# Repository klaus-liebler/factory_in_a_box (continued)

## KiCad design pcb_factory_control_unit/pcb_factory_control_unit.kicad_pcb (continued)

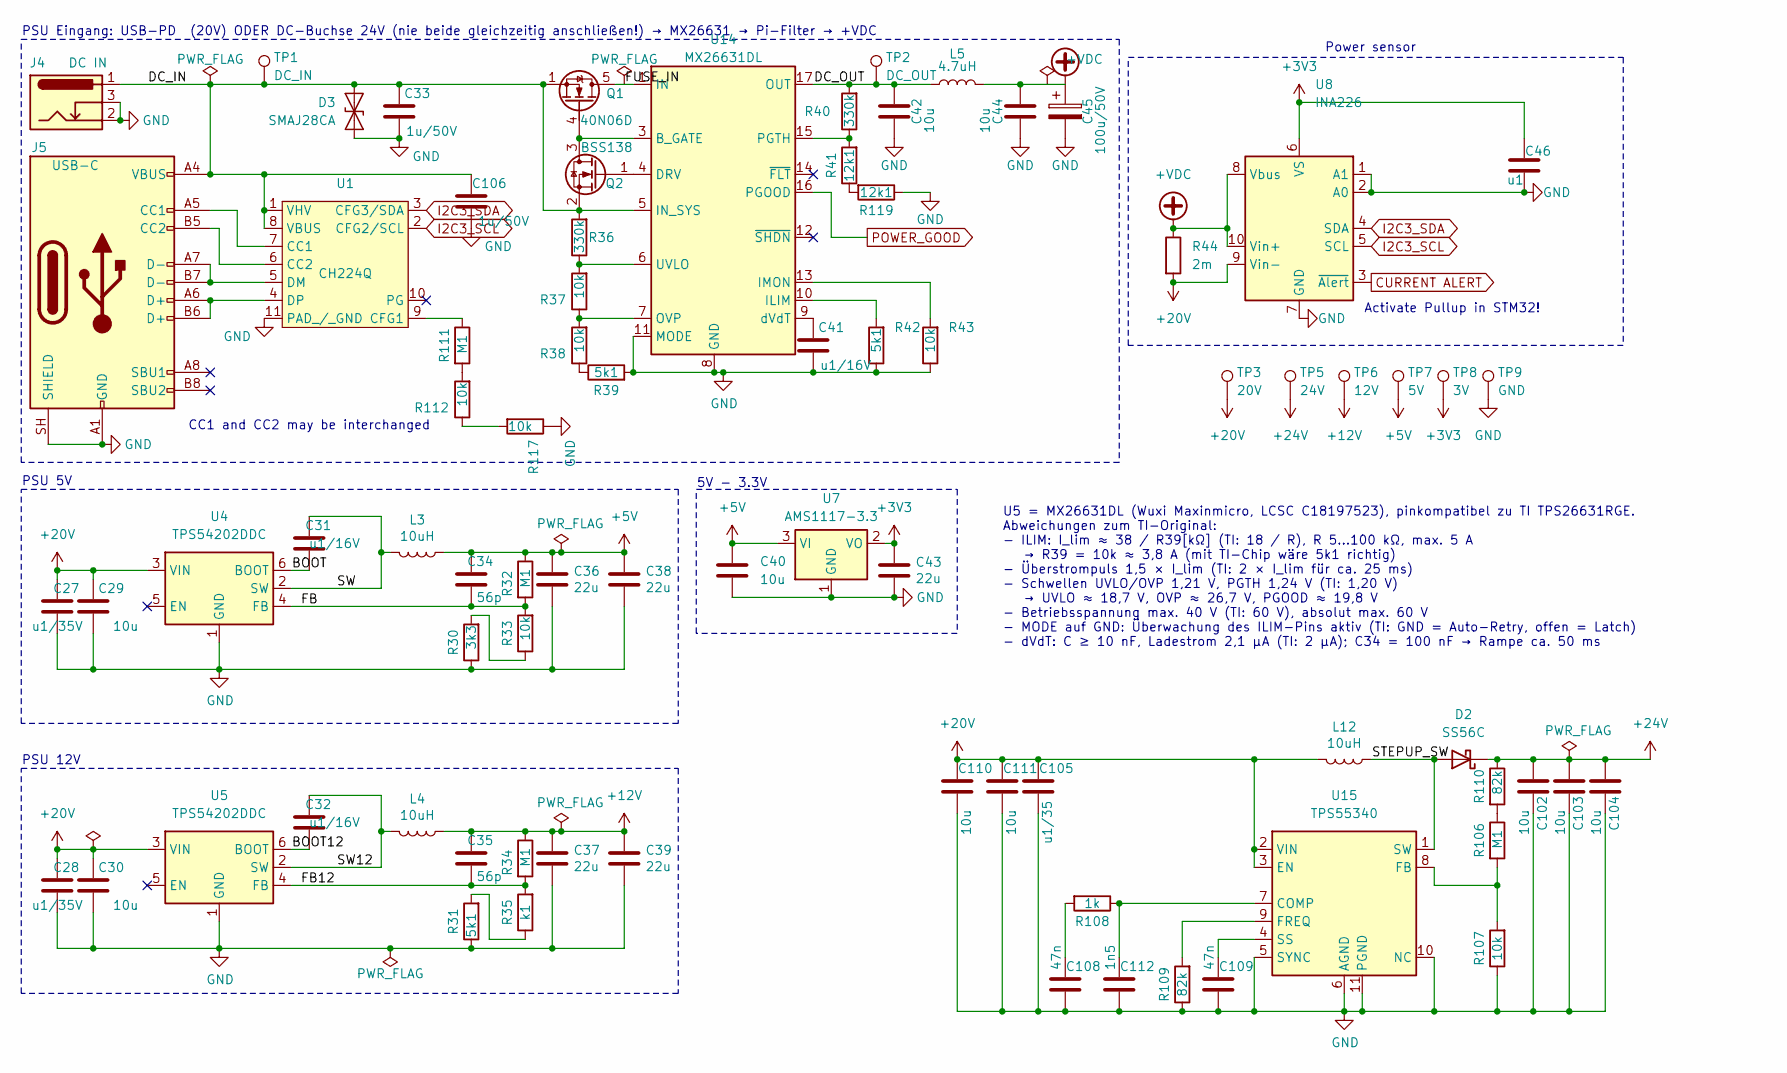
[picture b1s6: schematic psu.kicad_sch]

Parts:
C27, C28: u1/35V; C_0805_2012Metric; MPN CC0805KRX7R9BB104; LCSC C49678
C29, C30, C40, C110, C111: 10u; C_0805_2012Metric; MPN CGA0805X5R106K500MT; LCSC C6119889
C31, C32, C41: u1/16V; C_0402_1005Metric; MPN CL05B104KO5NNNC; LCSC C1525
C33, C106: 1u/50V; C_0805_2012Metric; MPN CL21B105KBFNNNE; LCSC C28323
C34, C35: 56p; C_0402_1005Metric; MPN CC0402JRNPO9BN560; LCSC C107007
C36, C37, C38, C39, C43: 22u; C_0805_2012Metric; MPN CL21A226MAQNNNE; LCSC C45783
C42, C44, C102, C103, C104: 10u; C_1210_3225Metric; MPN GRM32ER71H106KA12L; LCSC C77102
C45: 100u/50V; CP_Elec_8x10; MPN EEE-FK1H101P; LCSC C178548
C46: u1; C_0402_1005Metric; MPN CL05B104KO5NNNC; LCSC C1525
C105: u1/35; C_0805_2012Metric; MPN CC0805KRX7R9BB104; LCSC C49678
C108, C109: 47n; C_0402_1005Metric; MPN CL05B473KO5NNNC; LCSC C307434
C112: 1n5; C_0402_1005Metric; MPN CL05B152KB5NNNC; LCSC C23967
D2: SS56C; D_SMC; LCSC C24138
D3: SMAJ28CA; D_SMA; MPN SMAJ28CA; LCSC C19077546
J4: DC IN; BarrelJack_Horizontal; MPN DC-005 2.0
J5: USB-C; USB_C_Receptacle_HRO_TYPE-C-31-M-12_smaller; MPN TYPE-C-31-M-12; LCSC C165948
L3, L4, L12: 10uH; L_Abracon_ASPI-0630LR; MPN FXL0650-100-M; LCSC C475521
L5: 4.7uH; L_Bourns_SRP1245A; LCSC C54620181
Q1: 40N06D; VSON-8_3.3x3.3mm_P0.65mm_NexFET; MPN 40N06D; LCSC C7543836
Q2: BSS138; SOT-23; MPN BSS138LT1G; LCSC C82045
R30: 3k3; R_0402_1005Metric; MPN 0402WGF3301TCE; LCSC C25890
R31, R39, R42: 5k1; R_0402_1005Metric; MPN 0402WGF5101TCE; LCSC C25905
R32, R34, R106, R111: M1; R_0402_1005Metric; MPN 0402WGF1003TCE; LCSC C25741
R33, R37, R38, R43, R107, R112, R117: 10k; R_0402_1005Metric; MPN 0402WGF1002TCE; LCSC C25744
R35: k1; R_0402_1005Metric; MPN 0402WGF1000TCE; LCSC C25076
R36, R40: 330k; R_0402_1005Metric; MPN 0402WGF3303TCE; LCSC C25778
R41, R119: 12k1; R_0402_1005Metric; LCSC C25852
R44: 2m; R_1206_3216Metric; LCSC C844294
R108: 1k; R_0402_1005Metric; MPN 0402WGF1001TCE; LCSC C11702
R109, R110: 82k; R_0402_1005Metric; MPN 0402WGF8202TCE; LCSC C4142
TP1: DC_IN; TestPoint_Loop_D1.80mm_Drill1.0mm_Beaded
TP2: DC_OUT; TestPoint_Loop_D1.80mm_Drill1.0mm_Beaded
TP3: 20V; TestPoint_Loop_D1.80mm_Drill1.0mm_Beaded
TP5: 24V; TestPoint_Loop_D1.80mm_Drill1.0mm_Beaded
TP6: 12V; TestPoint_Loop_D1.80mm_Drill1.0mm_Beaded
TP7: 5V; TestPoint_Loop_D1.80mm_Drill1.0mm_Beaded
TP8: 3V; TestPoint_Loop_D1.80mm_Drill1.0mm_Beaded
TP9: GND; TestPoint_Loop_D1.80mm_Drill1.0mm_Beaded
U1: CH224Q; Texas_DSQ0010A_WSON-10-1EP_2x2mm_P0.4mm_EP0.9x1.5mm_Thermal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; LCSC C46061833
U4, U5: TPS54202DDC; SOT-23-6; MPN TPS54202DDCR; LCSC C191884
U7: AMS1117-3.3; SOT-223-3_TabPin2; LCSC C6186
U8: INA226; TSSOP-10_3x3mm_P0.5mm; LCSC C49851
U14: MX26631DL; Texas_RGE0024H_VQFN-24-1EP_4x4mm_P0.5mm_EP2.7x2.7mm_Thermal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; MPN MX26631DL; LCSC C18197523
U15: TPS55340; WQFN-16-1EP_3x3mm_P0.5mm_EP1.68x1.68mm_ThermalVias; MPN TPS55340RTER; LCSC C169167

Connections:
+3V3: C43.1, C46.1, TP8.1 (1_1), U7.2 (VO), U8.6 (VS); also elsewhere on the board
+5V: C34.2, C36.1, C38.1, C40.1, L3.1, R32.1, TP7.1 (1_1), U7.3 (VI); also elsewhere on the board
+12V: C35.2, C37.1, C39.1, L4.1, R34.1, TP6.1 (1_1); also elsewhere on the board
+20V: C27.2, C28.2, C29.2, C30.2, C105.2, C110.2, C111.2, L12.2, R44.2, TP3.1 (1_1), U4.3 (VIN), U5.3 (VIN), U8.9 (Vin-), U15.2 (VIN), U15.3 (EN); also elsewhere on the board
+24V: C102.1, C103.1, C104.1, D2.1 (K), R110.1, TP5.1 (1_1); also elsewhere on the board
+VDC: C44.1, C45.1, L5.2, R44.1, U8.8 (Vbus), U8.10 (Vin+)
/psu/BOOT: C31.1, U4.6 (BOOT)
/psu/BOOT12: C32.1, U5.6 (BOOT)
/psu/DC_IN: C33.2, C106.2, D3.2 (A2), J4.1, J5.A4 (VBUS), J5.A9 (VBUS), J5.B4 (VBUS), J5.B9 (VBUS), Q1.1 (S), Q1.2 (S), Q1.3 (S), Q2.2 (S), R36.2, TP1.1 (1_1), U1.1 (VHV), U1.8 (VBUS), U14.5 (IN_SYS)
/psu/DC_OUT: C42.1, L5.1, R40.2, TP2.1 (1_1), U14.17 (OUT), U14.18 (OUT)
/psu/FB: C34.1, R32.2, R33.2, U4.4 (FB)
/psu/FB12: C35.1, R34.2, R35.2, U5.4 (FB)
/psu/FUSE_IN: Q1.5 (D), U14.1 (IN), U14.2 (IN)
/psu/STEPUP_SW: D2.2 (A), L12.1, U15.1 (SW), U15.15 (SW), U15.16 (SW)
/psu/SW: C31.2, L3.2, U4.2 (SW)
/psu/SW12: C32.2, L4.2, U5.2 (SW)
CURRENT ALERT: U8.3 (~Alert); also elsewhere on the board
GND: C27.1, C28.1, C29.1, C30.1, C33.1, C36.2, C37.2, C38.2, C39.2, C40.2, C41.1, C42.2, C43.2, C44.2, C45.2, C46.2, C102.2, C103.2, C104.2, C105.1, C106.1, C108.1, C109.1, C110.1, C111.1, C112.1, D3.1 (A1), J4.2, J4.3, J5.A1 (GND), J5.A12 (GND), J5.B1 (GND), J5.B12 (GND), J5.SH (SHIELD), R30.1, R31.1, R39.2, R42.1, R43.1, R107.1, R109.1, R117.1, R119.1, TP9.1 (1_1), U1.11 (PAD_/_GND), U4.1 (GND), U5.1 (GND), U7.1 (GND), U8.1 (A1), U8.2 (A0), U8.7 (GND), U14.8 (GND), U14.11 (MODE), U14.25 (GND), U15.5 (SYNC), U15.6 (AGND), U15.10 (NC), U15.11 (PGND), U15.12 (PGND), U15.13 (PGND), U15.14 (NC), U15.17 (AGND); also elsewhere on the board
I2C3_SCL: U1.2 (CFG2/SCL), U8.5 (SCL); also elsewhere on the board
I2C3_SDA: U1.3 (CFG3/SDA), U8.4 (SDA); also elsewhere on the board
unnamed: C108.2, R108.2
unnamed: J5.A5 (CC1), U1.7 (CC1)
unnamed: J5.B5 (CC2), U1.6 (CC2)
unnamed: Q1.4 (G), Q2.3 (D), U14.3 (B_GATE)
unnamed: Q2.1 (G), U14.4 (DRV)
unnamed: R30.2, R33.1
unnamed: R31.2, R35.1
unnamed: R38.1, R39.1
unnamed: R106.1, R110.2
unnamed: R111.2, R112.2
unnamed: R112.1, R117.2
unnamed: R41.1, R119.2
unnamed: R111.1, U1.9 (CFG1)
unnamed: J5.A7 (D-), J5.B7 (D-), U1.5 (DM)
unnamed: J5.A6 (D+), J5.B6 (D+), U1.4 (DP)
unnamed: R42.2, U14.10 (ILIM)
unnamed: R43.2, U14.13 (IMON)
unnamed: R37.1, R38.2, U14.7 (OVP)
unnamed: R40.1, R41.2, U14.15 (PGTH)
unnamed: R36.1, R37.2, U14.6 (UVLO)
unnamed: C41.2, U14.9 (dVdT)
unnamed: C112.2, R108.1, U15.7 (COMP)
unnamed: R106.2, R107.2, U15.8 (FB)
unnamed: R109.2, U15.9 (FREQ)
unnamed: C109.2, U15.4 (SS)
POWER_GOOD: U14.16 (PGOOD); also elsewhere on the board

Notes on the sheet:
PSU 5V
Power sensor
U5 = MX26631DL (Wuxi Maxinmicro, LCSC C18197523), pinkompatibel zu TI TPS26631RGE. Abweichungen zum TI-Original: - ILIM: I_lim ≈ 38 / R39[kΩ] (TI: 18 / R), R 5…100 kΩ, max. 5 A → R39 = 10k ≈ 3,8 A (mit TI-Chip wäre 5k1 richtig) - Überstrompuls 1,5 × I_lim (TI: 2 × I_lim für ca. 25 ms) - Schwellen U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
PSU Eingang: USB-PD (20V) ODER DC-Buchse 24V (nie beide gleichzeitig anschließen!) → MX26631 → Pi-Filter → +VDC
PSU 12V
Activate Pullup in STM32!
CC1 and CC2 may be interchanged
5V - 3.3V

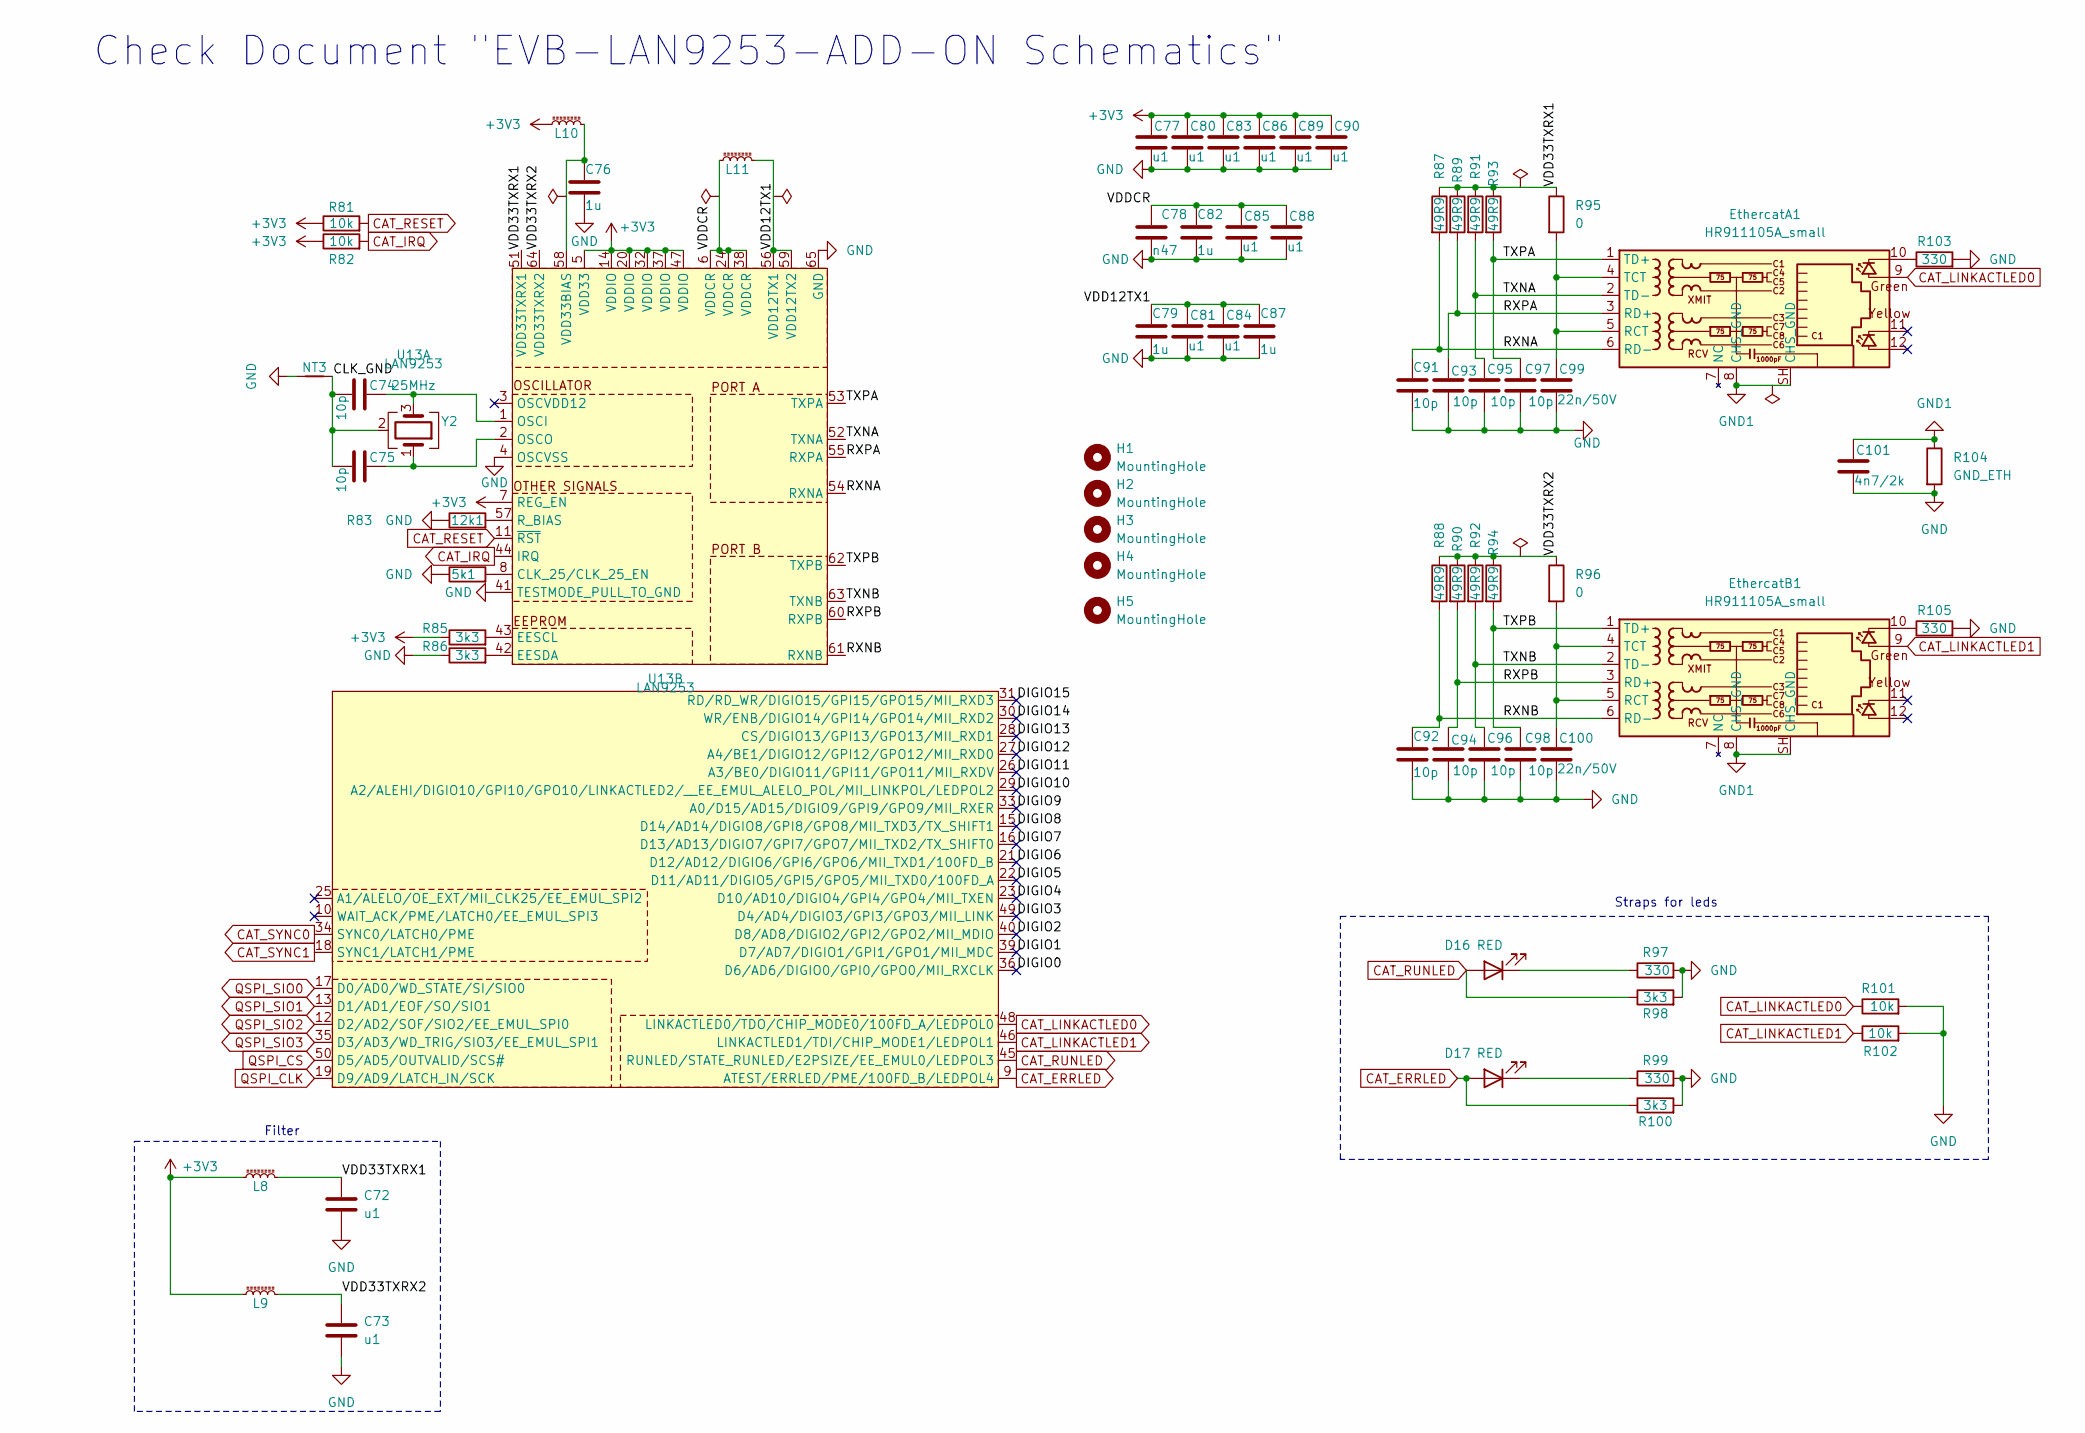
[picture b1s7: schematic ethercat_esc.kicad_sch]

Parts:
C72, C73, C77, C80, C81, C83, C84, C85, C86, C88, C89, C90: u1; C_0402_1005Metric; MPN CL05B104KO5NNNC; LCSC C1525
C74, C75, C91, C92, C93, C94, C95, C96, C97, C98: 10p; C_0402_1005Metric; MPN CC0402JRNPO9BN100; LCSC C106199
C76, C79, C82, C87: 1u; C_0402_1005Metric; MPN CL05A105KA5NQNC; LCSC C52923
C78: n47; C_0402_1005Metric; MPN GRM1555C1H471JA01D; LCSC C76971
C99, C100: 22n/50V; C_0402_1005Metric; MPN 0402B223K500NT; LCSC C1532
C101: 4n7/2k; C_0805_2012Metric_Pad1.18x1.45mm_HandSolder
D16, D17: RED; LED_1206_3216Metric_ReverseMount_Hole1.8x2.4mm; MPN P2-1206RTCS2-0.9T-F; LCSC C2827254
EthercatA1: HR911105A_small; RJ45_HANRUN_HR911105A; LCSC C12074
EthercatB1: HR911105A_small; RJ45_HANRUN_HR911105A; LCSC C12074
H1, H2, H3, H4: MountingHole; MountingHole_4.3mm_M4_DIN965
H5: MountingHole; barrel_jack_positive_polarity
L8, L9, L10, L11: 220R@100M; L_0603_1608Metric; MPN BLM18PG221SN1D; LCSC C80165
NT3: NetTie_2; NetTie-2_SMD_Pad0.5mm
R81, R82, R101, R102: 10k; R_0402_1005Metric; MPN 0402WGF1002TCE; LCSC C25744
R83: 12k1; R_0402_1005Metric; LCSC C25852
R84: 5k1; R_0402_1005Metric; MPN 0402WGF5101TCE; LCSC C25905
R85, R86, R98, R100: 3k3; R_0402_1005Metric; MPN 0402WGF3301TCE; LCSC C25890
R87, R88, R89, R90, R91, R92, R93, R94: 49R9; R_0402_1005Metric; LCSC C25120
R95, R96: 0; R_0805_2012Metric_Pad1.20x1.40mm_HandSolder; MPN 0805W8F0000T5E; LCSC C17477
R97, R99, R103, R105: 330; R_0402_1005Metric; MPN 0402WGF3300TCE; LCSC C25104
R104: GND_ETH; R_0805_2012Metric_Pad1.20x1.40mm_HandSolder
U13: LAN9253; QFN-64-1EP_9x9mm_P0.5mm_EP6x6mm_ThermalVias; MPN LAN9253-I/R4X; LCSC C5745149
Y2: 25MHz; Crystal_SMD_2016-4Pin_2.0x1.6mm; LCSC C19711739

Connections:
+3V3: C77.1, C80.1, C83.1, C86.1, C89.1, C90.1, L8.1, L9.1, L10.1, R81.1, R82.1, R85.1, U13.5 (VDD33), U13.7 (REG_EN), U13.14 (VDDIO), U13.20 (VDDIO), U13.32 (VDDIO), U13.37 (VDDIO), U13.47 (VDDIO); also elsewhere on the board
/EtherCAT/CLK_GND: C74.2, C75.2, NT3.2, Y2.2 (G), Y2.4 (G)
/EtherCAT/DIGIO0: U13.36 (D6/AD6/DIGIO0/GPI0/GPO0/MII_RXCLK)
/EtherCAT/DIGIO1: U13.39 (D7/AD7/DIGIO1/GPI1/GPO1/MII_MDC)
/EtherCAT/DIGIO2: U13.40 (D8/AD8/DIGIO2/GPI2/GPO2/MII_MDIO)
/EtherCAT/DIGIO3: U13.49 (D4/AD4/DIGIO3/GPI3/GPO3/MII_LINK)
/EtherCAT/DIGIO4: U13.23 (D10/AD10/DIGIO4/GPI4/GPO4/MII_TXEN)
/EtherCAT/DIGIO5: U13.22 (D11/AD11/DIGIO5/GPI5/GPO5/MII_TXD0/100F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)
/EtherCAT/DIGIO6: U13.21 (D12/AD12/DIGIO6/GPI6/GPO6/MII_TXD1/100F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)
/EtherCAT/DIGIO7: U13.16 (D13/AD13/DIGIO7/GPI7/GPO7/MII_TXD2/TX_S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)
/EtherCAT/DIGIO8: U13.15 (D14/AD14/DIGIO8/GPI8/GPO8/MII_TXD3/TX_S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)
/EtherCAT/DIGIO9: U13.33 (A0/D15/AD15/DIGIO9/GPI9/GPO9/MII_RXER)
/EtherCAT/DIGIO10: U13.29 (A2/ALEHI/DIGIO10/GPI10/GPO10/LINKACTLED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)
/EtherCAT/DIGIO11: U13.26 (A3/BE0/DIGIO11/GPI11/GPO11/MII_RXDV)
/EtherCAT/DIGIO12: U13.27 (A4/BE1/DIGIO12/GPI12/GPO12/MII_RXD0)
/EtherCAT/DIGIO13: U13.28 (CS/DIGIO13/GPI13/GPO13/MII_RXD1)
/EtherCAT/DIGIO14: U13.30 (WR/ENB/DIGIO14/GPI14/GPO14/MII_RXD2)
/EtherCAT/DIGIO15: U13.31 (RD/RD_WR/DIGIO15/GPI15/GPO15/MII_RXD3)
/EtherCAT/RXNA: C91.1, EthercatA1.6 (RD-), R87.2, U13.54 (RXNA)
/EtherCAT/RXNB: C92.1, EthercatB1.6 (RD-), R88.2, U13.61 (RXNB)
/EtherCAT/RXPA: C93.1, EthercatA1.3 (RD+), R89.2, U13.55 (RXPA)
/EtherCAT/RXPB: C94.1, EthercatB1.3 (RD+), R90.2, U13.60 (RXPB)
/EtherCAT/TXNA: C95.1, EthercatA1.2 (TD-), R91.2, U13.52 (TXNA)
/EtherCAT/TXNB: C96.1, EthercatB1.2 (TD-), R92.2, U13.63 (TXNB)
/EtherCAT/TXPA: C97.1, EthercatA1.1 (TD+), R93.2, U13.53 (TXPA)
/EtherCAT/TXPB: C98.1, EthercatB1.1 (TD+), R94.2, U13.62 (TXPB)
/EtherCAT/VDD12TX1: C79.1, C81.1, C84.1, C87.1, L11.2, U13.56 (VDD12TX1), U13.59 (VDD12TX2)
/EtherCAT/VDD33TXRX1: C72.1, L8.2, R87.1, R89.1, R91.1, R93.1, R95.1, U13.51 (VDD33TXRX1)
/EtherCAT/VDD33TXRX2: C73.1, L9.2, R88.1, R90.1, R92.1, R94.1, R96.1, U13.64 (VDD33TXRX2)
/EtherCAT/VDDCR: C78.1, C82.1, C85.1, C88.1, L11.1, U13.6 (VDDCR), U13.24 (VDDCR), U13.38 (VDDCR)
CAT_ERRLED: D17.2 (A), R100.1, U13.9 (ATEST/ERRLED/PME/100FD_B/LEDPOL4)
CAT_IRQ: R82.2, U13.44 (IRQ); also elsewhere on the board
CAT_LINKACTLED0: EthercatA1.9, R101.1, U13.48 (LINKACTLED0/TDO/CHIP_MODE0/100FD_A/LEDP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)
CAT_LINKACTLED1: EthercatB1.9, R102.1, U13.46 (LINKACTLED1/TDI/CHIP_MODE1/LEDPOL1)
CAT_RESET: R81.2, U13.11 (~RST); also elsewhere on the board
CAT_RUNLED: D16.2 (A), R98.1, U13.45 (RUNLED/STATE_RUNLED/E2PSIZE/EE_EMUL0/LE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)
CAT_SYNC0: U13.34 (SYNC0/LATCH0/PME); also elsewhere on the board
CAT_SYNC1: U13.18 (SYNC1/LATCH1/PME); also elsewhere on the board
GND: C72.2, C73.2, C76.2, C77.2, C78.2, C79.2, C80.2, C81.2, C82.2, C83.2, C84.2, C85.2, C86.2, C87.2, C88.2, C89.2, C90.2, C91.2, C92.2, C93.2, C94.2, C95.2, C96.2, C97.2, C98.2, C99.2, C100.2, C101.2, NT3.1, R83.1, R84.1, R86.1, R97.2, R98.2, R99.2, R100.2, R101.2, R102.2, R103.2, R104.2, R105.2, U13.4 (OSCVSS), U13.41 (TESTMODE_PULL_TO_GND), U13.65 (GND); also elsewhere on the board
GND1: C101.1, EthercatA1.8 (CHS_GND), EthercatA1.SH (CHS_GND), EthercatB1.8 (CHS_GND), EthercatB1.SH (CHS_GND), R104.1; also elsewhere on the board
unnamed: D16.1 (K), R97.1
unnamed: D17.1 (K), R99.1
unnamed: EthercatA1.10, R103.1
unnamed: C99.1, EthercatA1.4 (TCT), EthercatA1.5 (RCT), R95.2
unnamed: EthercatB1.10, R105.1
unnamed: C100.1, EthercatB1.4 (TCT), EthercatB1.5 (RCT), R96.2
unnamed: R84.2, U13.8 (CLK_25/CLK_25_EN)
unnamed: R85.2, U13.43 (EESCL)
unnamed: R86.2, U13.42 (EESDA)
unnamed: C74.1, U13.1 (OSCI), Y2.3
unnamed: C75.1, U13.2 (OSCO), Y2.1
unnamed: R83.2, U13.57 (R_BIAS)
unnamed: C76.1, L10.2, U13.58 (VDD33BIAS)
QSPI_CLK: U13.19 (D9/AD9/LATCH_IN/SCK); also elsewhere on the board
QSPI_CS: U13.50 (D5/AD5/OUTVALID/SCS#); also elsewhere on the board
QSPI_SIO0: U13.17 (D0/AD0/WD_STATE/SI/SIO0); also elsewhere on the board
QSPI_SIO1: U13.13 (D1/AD1/EOF/SO/SIO1); also elsewhere on the board
QSPI_SIO2: U13.12 (D2/AD2/SOF/SIO2/EE_EMUL_SPI0); also elsewhere on the board
QSPI_SIO3: U13.35 (D3/AD3/WD_TRIG/SIO3/EE_EMUL_SPI1); also elsewhere on the board

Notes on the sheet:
Straps for leds
Filter
Check Document "EVB-LAN9253-ADD-ON Schematics"

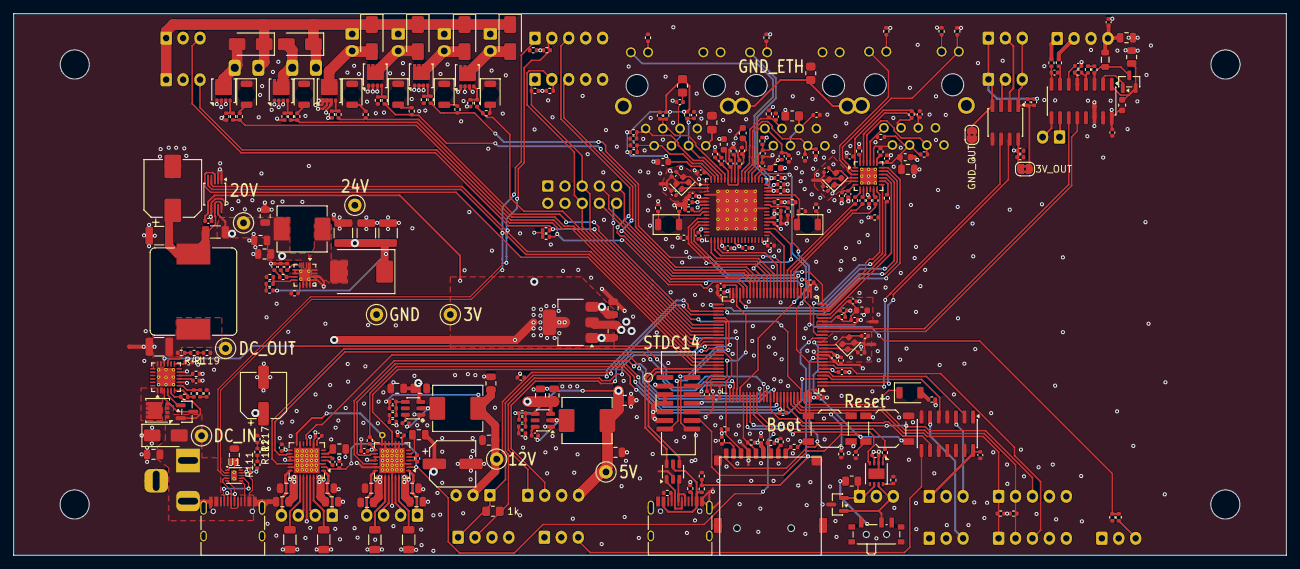
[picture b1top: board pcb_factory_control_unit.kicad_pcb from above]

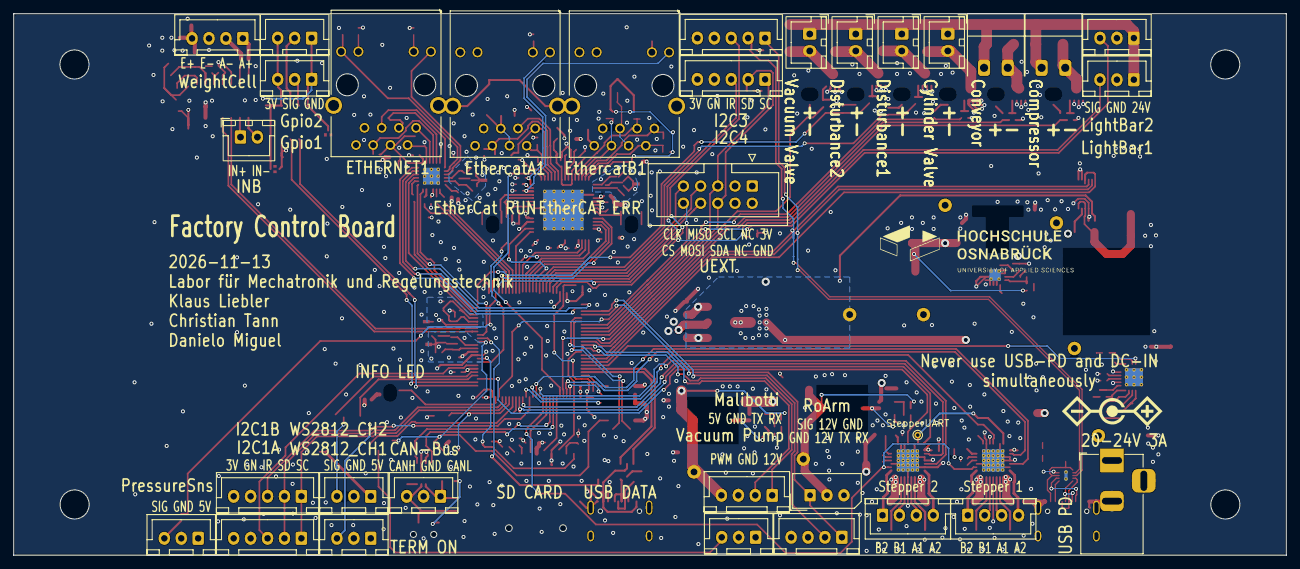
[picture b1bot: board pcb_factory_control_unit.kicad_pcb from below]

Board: 4 copper layers, 188.0 x 80.0 mm, 352 parts (33 on the bottom side), 252 nets.

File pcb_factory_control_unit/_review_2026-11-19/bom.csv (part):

"Reference","Value","Footprint","MPN","LCSC","QUANTITY","DNP","Manufacturer"
"C1","u1","Capacitor_SMD:C_0402_1005Metric","CL05B104KO5NNNC","C1525","1","","Samsung Electro-Mechanics"
"C2","u1","Capacitor_SMD:C_0402_1005Metric","CL05B104KO5NNNC","C1525","1","","Samsung Electro-Mechanics"
"C3","u1","Capacitor_SMD:C_0402_1005Metric","CL05B104KO5NNNC","C1525","1","","Samsung Electro-Mechanics"
"C4","1u","Capacitor_SMD:C_0402_1005Metric","CL05A105KA5NQNC","C52923","1","","Samsung Electro-Mechanics"
"C5","u1","Capacitor_SMD:C_0402_1005Metric","CL05B104KO5NNNC","C1525","1","","Samsung Electro-Mechanics"
"C6","u1","Capacitor_SMD:C_0402_1005Metric","CL05B104KO5NNNC","C1525","1","","Samsung Electro-Mechanics"
"C7","u1","Capacitor_SMD:C_0402_1005Metric","CL05B104KO5NNNC","C1525","1","","Samsung Electro-Mechanics"
"C8","u1","Capacitor_SMD:C_0402_1005Metric","CL05B104KO5NNNC","C1525","1","","Samsung Electro-Mechanics"
"C9","u1","Capacitor_SMD:C_0402_1005Metric","CL05B104KO5NNNC","C1525","1","","Samsung Electro-Mechanics"
"C11","4u7","Capacitor_SMD:C_0402_1005Metric","","C307423","1","",""
"C12","u1","Capacitor_SMD:C_0402_1005Metric","CL05B104KO5NNNC","C1525","1","","Samsung Electro-Mechanics"
"C13","2u2","Capacitor_SMD:C_0402_1005Metric","CL05A225MQ5NSNC","C12530","1","","Samsung Electro-Mechanics"
"C14","1u","Capacitor_SMD:C_0402_1005Metric","CL05A105KA5NQNC","C52923","1","","Samsung Electro-Mechanics"
"C15","2u2","Capacitor_SMD:C_0402_1005Metric","CL05A225MQ5NSNC","C12530","1","","Samsung Electro-Mechanics"
"C16","u1","Capacitor_SMD:C_0402_1005Metric","CL05B104KO5NNNC","C1525","1","","Samsung Electro-Mechanics"
"C17","u1","Capacitor_SMD:C_0402_1005Metric","CL05B104KO5NNNC","C1525","1","","Samsung Electro-Mechanics"
"C18","10p","Capacitor_SMD:C_0402_1005Metric","CC0402JRNPO9BN100","C106199","1","","YAGEO"
"C19","10n","Capacitor_SMD:C_0402_1005Metric","FCC0402B103K500AT","C5137480","1","","FOJAN"
"C20","10p","Capacitor_SMD:C_0402_1005Metric","CC0402JRNPO9BN100","C106199","1","","YAGEO"
"C21","1u","Capacitor_SMD:C_0402_1005Metric","CL05A105KA5NQNC","C52923","1","","Samsung Electro-Mechanics"
"C22","n47","Capacitor_SMD:C_0402_1005Metric","GRM1555C1H471JA01D","C76971","1","","Murata Electronics"
"C23","10n","Capacitor_SMD:C_0402_1005Metric","FCC0402B103K500AT","C5137480","1","","FOJAN"
"C24","10n","Capacitor_SMD:C_0402_1005Metric","FCC0402B103K500AT","C5137480","1","","FOJAN"
"C25","10u","Capacitor_SMD:C_0805_2012Metric","CGA0805X5R106K500MT","C6119889","1","","HRE"
"C26","22n/50V","Capacitor_SMD:C_0402_1005Metric","0402B223K500NT","C1532","1","","FH(Guangdong Fenghua Advanced Tech)"
"C27","u1/35V","Capacitor_SMD:C_0805_2012Metric","CC0805KRX7R9BB104","C49678","1","","YAGEO"
"C28","u1/35V","Capacitor_SMD:C_0805_2012Metric","CC0805KRX7R9BB104","C49678","1","","YAGEO"
"C29","10u","Capacitor_SMD:C_0805_2012Metric","CGA0805X5R106K500MT","C6119889","1","","HRE"
"C30","10u","Capacitor_SMD:C_0805_2012Metric","CGA0805X5R106K500MT","C6119889","1","","HRE"
"C31","u1/16V","Capacitor_SMD:C_0402_1005Metric","CL05B104KO5NNNC","C1525","1","","Samsung Electro-Mechanics"
"C32","u1/16V","Capacitor_SMD:C_0402_1005Metric","CL05B104KO5NNNC","C1525","1","","Samsung Electro-Mechanics"
"C33","1u/50V","Capacitor_SMD:C_0805_2012Metric","CL21B105KBFNNNE","C28323","1","","Samsung Electro-Mechanics"
"C34","56p","Capacitor_SMD:C_0402_1005Metric","CC0402JRNPO9BN560","C107007","1","","YAGEO"
"C35","56p","Capacitor_SMD:C_0402_1005Metric","CC0402JRNPO9BN560","C107007","1","","YAGEO"
"C36","22u","Capacitor_SMD:C_0805_2012Metric","CL21A226MAQNNNE","C45783","1","","Samsung Electro-Mechanics"
"C37","22u","Capacitor_SMD:C_0805_2012Metric","CL21A226MAQNNNE","C45783","1","","Samsung Electro-Mechanics"
"C38","22u","Capacitor_SMD:C_0805_2012Metric","CL21A226MAQNNNE","C45783","1","","Samsung Electro-Mechanics"
"C39","22u","Capacitor_SMD:C_0805_2012Metric","CL21A226MAQNNNE","C45783","1","","Samsung Electro-Mechanics"
"C40","10u","Capacitor_SMD:C_0805_2012Metric","CGA0805X5R106K500MT","C6119889","1","","HRE"
"C41","u1/16V","Capacitor_SMD:C_0402_1005Metric","CL05B104KO5NNNC","C1525","1","","Samsung Electro-Mechanics"
"C42","10u","Capacitor_SMD:C_1210_3225Metric","GRM32ER71H106KA12L","C77102","1","","Murata"
"C43","22u","Capacitor_SMD:C_0805_2012Metric","CL21A226MAQNNNE","C45783","1","","Samsung Electro-Mechanics"
"C44","10u","Capacitor_SMD:C_1210_3225Metric","GRM32ER71H106KA12L","C77102","1","","Murata"
"C45","100u/50V","Capacitor_SMD:CP_Elec_8x10","EEE-FK1H101P","C178548","1","","Panasonic"
"C46","u1","Capacitor_SMD:C_0402_1005Metric","CL05B104KO5NNNC","C1525","1","","Samsung Electro-Mechanics"
"C47","u1/50V","Capacitor_SMD:C_0805_2012Metric","CC0805KRX7R9BB104","C49678","1","","YAGEO"
"C48","u1/50V","Capacitor_SMD:C_0805_2012Metric","CC0805KRX7R9BB104","C49678","1","","YAGEO"
"C49","u1","Capacitor_SMD:C_0402_1005Metric","CL05B104KO5NNNC","C1525","1","","Samsung Electro-Mechanics"
"C50","u1","Capacitor_SMD:C_0402_1005Metric","CL05B104KO5NNNC","C1525","1","","Samsung Electro-Mechanics"
"C51","u1/35V","Capacitor_SMD:C_0805_2012Metric","CC0805KRX7R9BB104","C49678","1","","YAGEO"
"C52","u1/35V","Capacitor_SMD:C_0805_2012Metric","CC0805KRX7R9BB104","C49678","1","","YAGEO"
"C53","u1/35V","Capacitor_SMD:C_0805_2012Metric","CC0805KRX7R9BB104","C49678","1","","YAGEO"
"C54","u1/35V","Capacitor_SMD:C_0805_2012Metric","CC0805KRX7R9BB104","C49678","1","","YAGEO"
"C55","2u2","Capacitor_SMD:C_0402_1005Metric","CL05A225MQ5NSNC","C12530","1","","Samsung Electro-Mechanics"
"C56","22n/50V","Capacitor_SMD:C_0402_1005Metric","0402B223K500NT","C1532","1","","FH(Guangdong Fenghua Advanced Tech)"
"C57","2u2","Capacitor_SMD:C_0402_1005Metric","CL05A225MQ5NSNC","C12530","1","","Samsung Electro-Mechanics"
"C58","22n/50V","Capacitor_SMD:C_0402_1005Metric","0402B223K500NT","C1532","1","","FH(Guangdong Fenghua Advanced Tech)"
"C59","22u/35V","Capacitor_SMD:C_0805_2012Metric","CGA0805X5R226M350MT","C6119901","1","","HRE"
"C60","22u/35V","Capacitor_SMD:C_0805_2012Metric","CGA0805X5R226M350MT","C6119901","1","","HRE"
"C61","22u/35V","Capacitor_SMD:C_0805_2012Metric","CGA0805X5R226M350MT","C6119901","1","","HRE"
"C62","22u/35V","Capacitor_SMD:C_0805_2012Metric","CGA0805X5R226M350MT","C6119901","1","","HRE"
"C63","u1","Capacitor_SMD:C_0402_1005Metric","CL05B104KO5NNNC","C1525","1","","Samsung Electro-Mechanics"
"C64","100uF","Capacitor_SMD:CP_Elec_6.3x7.7","RVT1V101M0607","C72478","1","","ROQANG"
"C65","100uF","Capacitor_SMD:CP_Elec_6.3x7.7","RVT1V101M0607","C72478","1","","ROQANG"
"C66","u1","Capacitor_SMD:C_0402_1005Metric","CL05B104KO5NNNC","C1525","1","","Samsung Electro-Mechanics"
"C67","10u","Capacitor_SMD:C_0805_2012Metric","CGA0805X5R106K500MT","C6119889","1","","HRE"
"C68","u1","Capacitor_SMD:C_0402_1005Metric","CL05B104KO5NNNC","C1525","1","","Samsung Electro-Mechanics"
"C69","10u","Capacitor_SMD:C_0805_2012Metric","CGA0805X5R106K500MT","C6119889","1","","HRE"
"C70","u1","Capacitor_SMD:C_0402_1005Metric","CL05B104KO5NNNC","C1525","1","","Samsung Electro-Mechanics"
"C71","u1","Capacitor_SMD:C_0402_1005Metric","CL05B104KO5NNNC","C1525","1","","Samsung Electro-Mechanics"
"C72","u1","Capacitor_SMD:C_0402_1005Metric","CL05B104KO5NNNC","C1525","1","","Samsung Electro-Mechanics"
"C73","u1","Capacitor_SMD:C_0402_1005Metric","CL05B104KO5NNNC","C1525","1","","Samsung Electro-Mechanics"
"C74","10p","Capacitor_SMD:C_0402_1005Metric","CC0402JRNPO9BN100","C106199","1","","YAGEO"
"C75","10p","Capacitor_SMD:C_0402_1005Metric","CC0402JRNPO9BN100","C106199","1","","YAGEO"
"C76","1u","Capacitor_SMD:C_0402_1005Metric","CL05A105KA5NQNC","C52923","1","","Samsung Electro-Mechanics"
"C77","u1","Capacitor_SMD:C_0402_1005Metric","CL05B104KO5NNNC","C1525","1","","Samsung Electro-Mechanics"
"C78","n47","Capacitor_SMD:C_0402_1005Metric","GRM1555C1H471JA01D","C76971","1","","Murata Electronics"
"C79","1u","Capacitor_SMD:C_0402_1005Metric","CL05A105KA5NQNC","C52923","1","","Samsung Electro-Mechanics"
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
